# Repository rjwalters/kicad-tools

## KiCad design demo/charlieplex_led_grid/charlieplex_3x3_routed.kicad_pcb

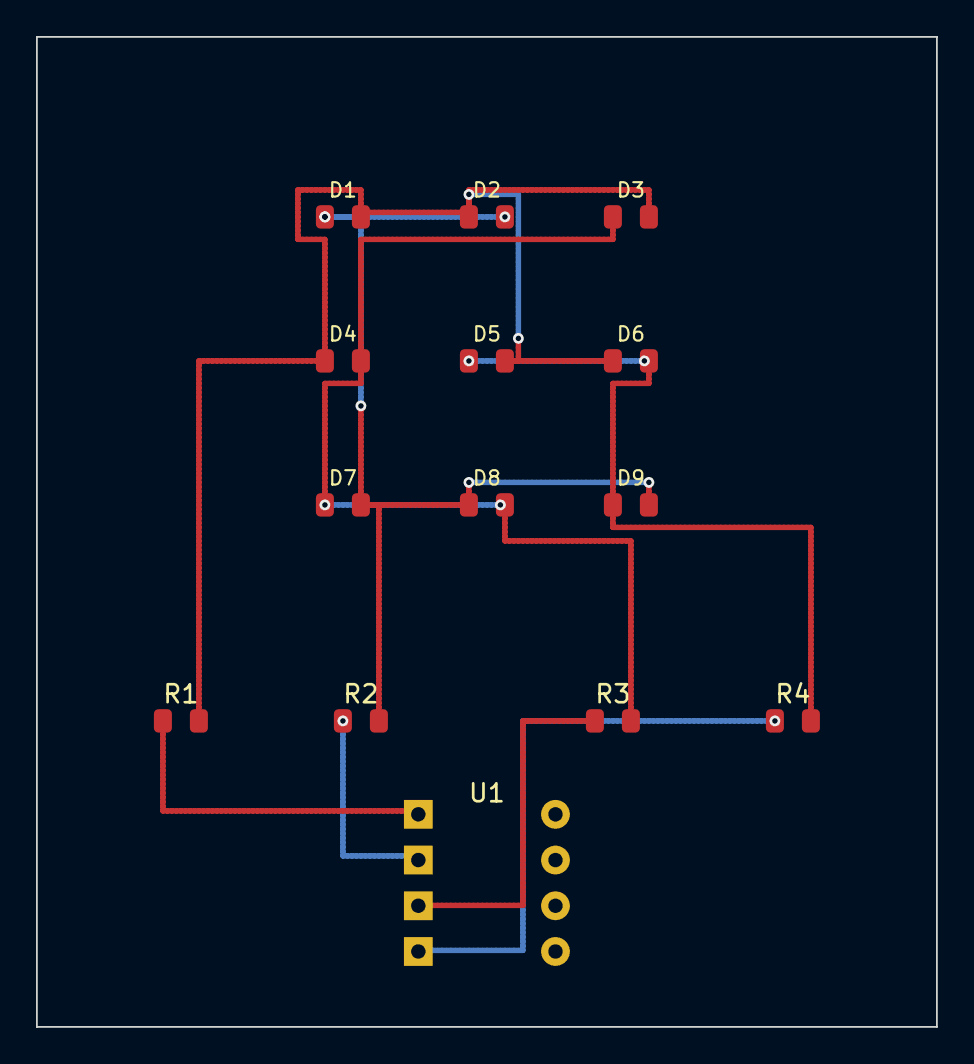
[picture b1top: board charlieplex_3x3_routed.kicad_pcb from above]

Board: 2 copper layers, 50.0 x 55.0 mm, 14 parts (0 on the bottom side), 8 nets.

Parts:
D1, D2, D3, D4, D5, D6, D7, D8, D9: LED; LED_0805_2012Metric
R1, R2, R3, R4: 330R; R_0805_2012Metric
U1: MCU; DIP-8_W7.62mm

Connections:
LINE_A: R1.1, U1.1
LINE_B: R2.1, U1.2
LINE_C: R3.1, U1.3
LINE_D: R4.1, U1.4
NODE_A: D1.2, D2.1, D3.2, D4.1, D5.2, D6.1, R1.2
NODE_B: D1.1, D2.2, D7.2, D8.1, D9.2, R2.2
NODE_C: D3.1, D4.2, D7.1, D8.2, R3.2
NODE_D: D5.1, D6.2, D9.1, R4.2

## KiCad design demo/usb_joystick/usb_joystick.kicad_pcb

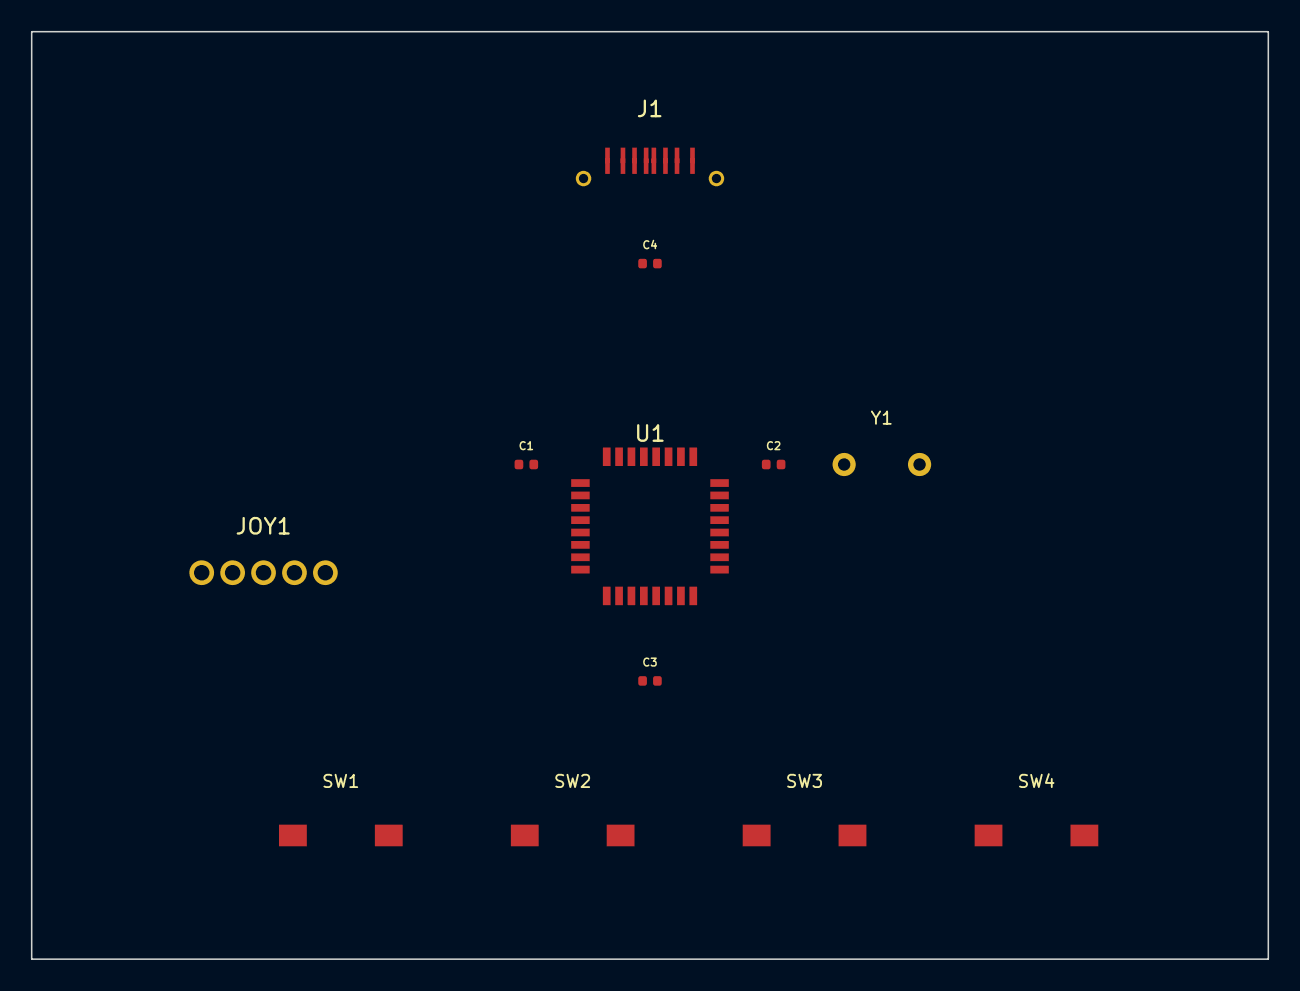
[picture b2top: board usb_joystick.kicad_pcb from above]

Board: 2 copper layers, 80.0 x 60.0 mm, 12 parts (0 on the bottom side), 16 nets, no tracks yet.

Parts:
C1, C2, C3, C4: 100nF; C_0402_1005Metric
J1: USB-C; USB_C_Receptacle_GCT_USB4105
JOY1: Joystick; Joystick_Analog
SW1, SW2, SW3, SW4: Button; SW_SPST_TL3342
U1: MCU; TQFP-32_7x7mm_P0.8mm
Y1: 16MHz; Crystal_HC49-U_Vertical

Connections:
BTN1: SW1.1, U1.12
BTN2: SW2.1, U1.13
BTN3: SW3.1, U1.14
BTN4: SW4.1, U1.15
GND: C1.2, C2.2, C3.2, C4.2, J1.A1, J1.A12, J1.B1, J1.B12, J1.S1, J1.S2, JOY1.1, SW1.2, SW2.2, SW3.2, SW4.2, U1.1, U1.7, U1.16, U1.23, U1.32
JOY_BTN: JOY1.5, U1.11
JOY_X: JOY1.3, U1.9
JOY_Y: JOY1.4, U1.10
USB_CC1: J1.A5, U1.30
USB_CC2: J1.B5, U1.31
USB_D+: J1.A6, J1.B6, U1.3
USB_D-: J1.A7, J1.B7, U1.2
VBUS: C4.1, J1.A4, J1.A9, J1.B4, J1.B9, U1.29
VCC: C1.1, C2.1, C3.1, JOY1.2, U1.4, U1.8, U1.17, U1.24
XTAL1: U1.5, Y1.1
XTAL2: U1.6, Y1.2

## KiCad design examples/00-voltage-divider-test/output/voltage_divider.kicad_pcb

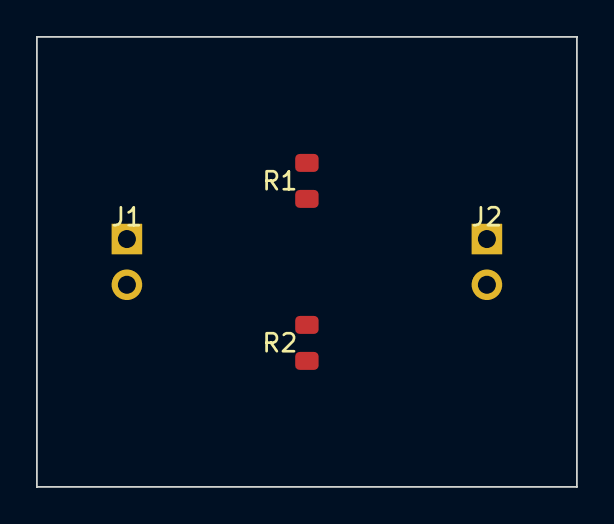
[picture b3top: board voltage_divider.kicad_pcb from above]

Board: 2 copper layers, 30.0 x 25.0 mm, 4 parts (0 on the bottom side), 3 nets, no tracks yet.

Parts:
J1, J2: Conn_01x02; PinHeader_1x02_P2.54mm_Vertical
R1, R2: 10k; R_0805_2012Metric

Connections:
GND: J1.2, J2.2, R2.2
VIN: J1.1, R1.1
VOUT: J2.1, R1.2, R2.1

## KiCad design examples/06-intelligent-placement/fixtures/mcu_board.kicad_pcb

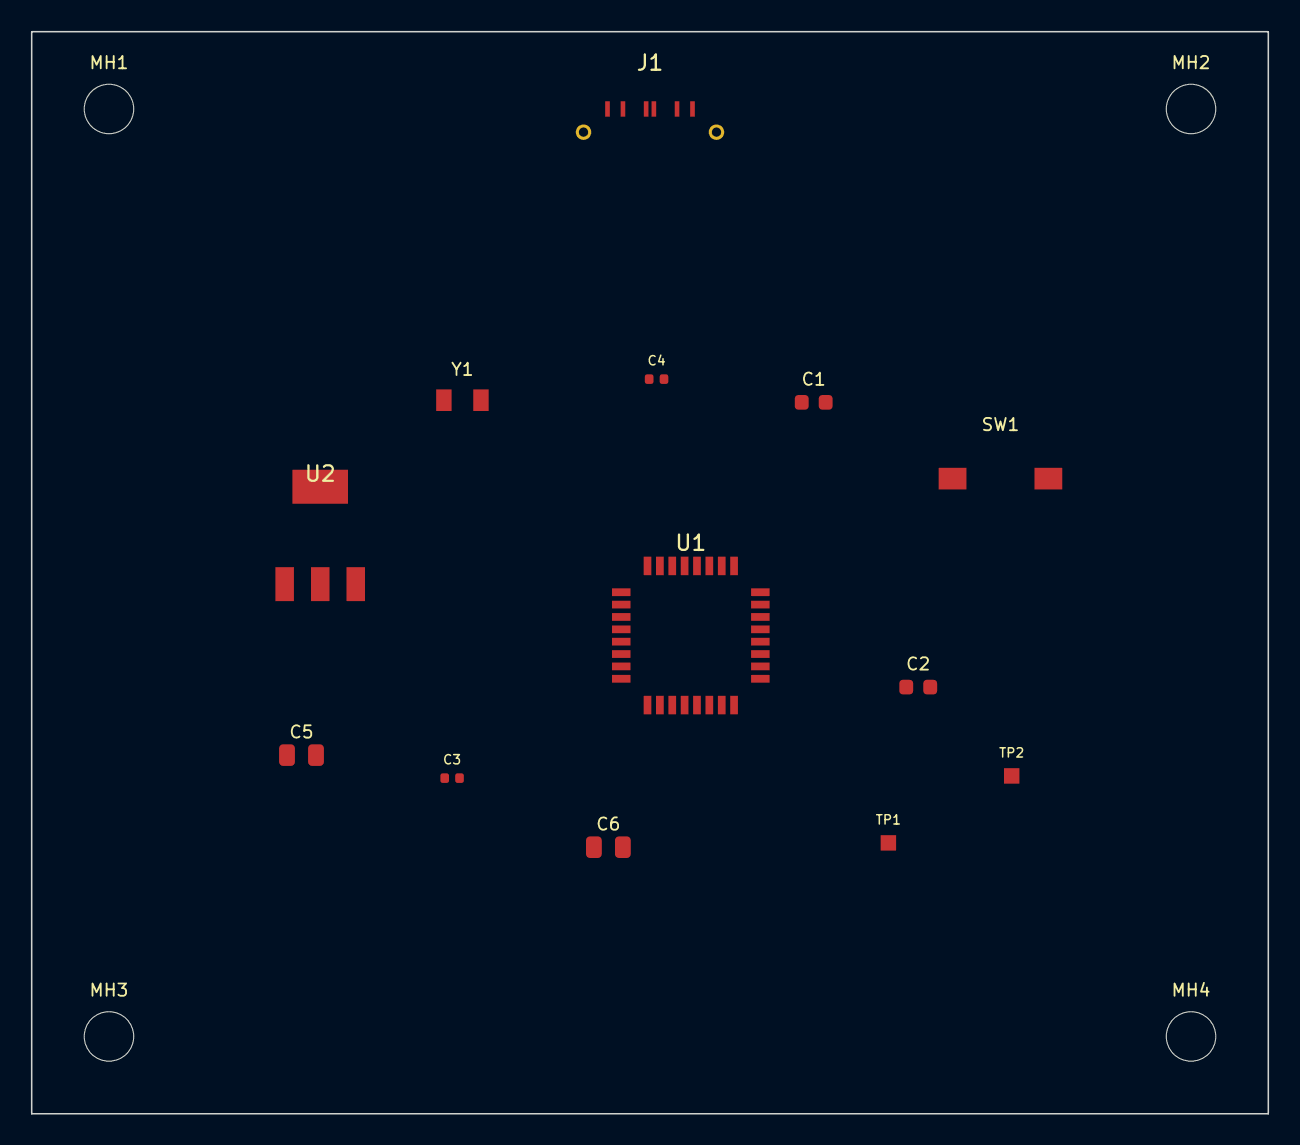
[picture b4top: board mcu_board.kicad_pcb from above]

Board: 2 copper layers, 80.0 x 70.0 mm, 17 parts (0 on the bottom side), 8 nets, no tracks yet.

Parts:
C1: 100nF; C_0603_1608Metric
C2: 10uF; C_0603_1608Metric
C3, C4: 20pF; C_0402_1005Metric
C5: 10uF; C_0805_2012Metric
C6: 22uF; C_0805_2012Metric
J1: USB-C; USB_C_Receptacle_GCT_USB4105
MH1, MH2, MH3, MH4: MountingHole; MountingHole_3.2mm_M3
SW1: RESET; SW_SPST_TL3342
TP1, TP2: TestPoint; TestPoint_Pad_1.0x1.0mm
U1: STM32F103; TQFP-32_7x7mm_P0.8mm
U2: AMS1117-3.3; SOT-223-3_TabPin2
Y1: 8MHz; Crystal_SMD_3215-2Pin_3.2x1.5mm

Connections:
GND: C1.2, C2.2, C3.2, C4.2, C5.2, C6.2, J1.A1, J1.A12, J1.S1, J1.S2, SW1.2, TP2.1, U1.1, U1.7, U1.16, U1.23, U1.25, U1.32, U2.1
GPIO1: SW1.1, U1.5
USB_D+: J1.A6, U1.27
USB_D-: J1.A7, U1.26
VCC: C1.1, C2.1, C6.1, TP1.1, U1.4, U1.8, U1.17, U1.24, U2.2, U2.4
VIN: C5.1, J1.A4, J1.A9, U2.3
XTAL1: C3.1, U1.2, Y1.1
XTAL2: C4.1, U1.3, Y1.2

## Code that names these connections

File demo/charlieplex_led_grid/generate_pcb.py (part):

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    pin_pitch = 2.54

    # Pin assignments:
    # 1: LINE_A (GPIO)
    # 2: LINE_B (GPIO)
    # 3: LINE_C (GPIO)
    # 4: LINE_D (GPIO)
    # 5: NC
    # 6: NC
    # 7: VCC
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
